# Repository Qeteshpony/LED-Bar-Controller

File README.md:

# Qeteshs 2-Color LED Bar Controller

[Hardware Documentation](https://qeteshpony.github.io/LED-Bar-Controller)

This controller replaces the cable bound remote control for a 2-Color USB LED bar and includes an ESP32-WROOM-32 for connecting it to home automation

The board also features a USB-C port for power, a 3-Pin PH2.0 plug for connecting the LED bar and four buttons to control power, brightness and light-temperature. 

All parts on the top side are selected from the JLCPCB basic library for cheap production. The ESP module and the connectors need manual soldering on the bottom side unless two-sided pcb assembly is used.

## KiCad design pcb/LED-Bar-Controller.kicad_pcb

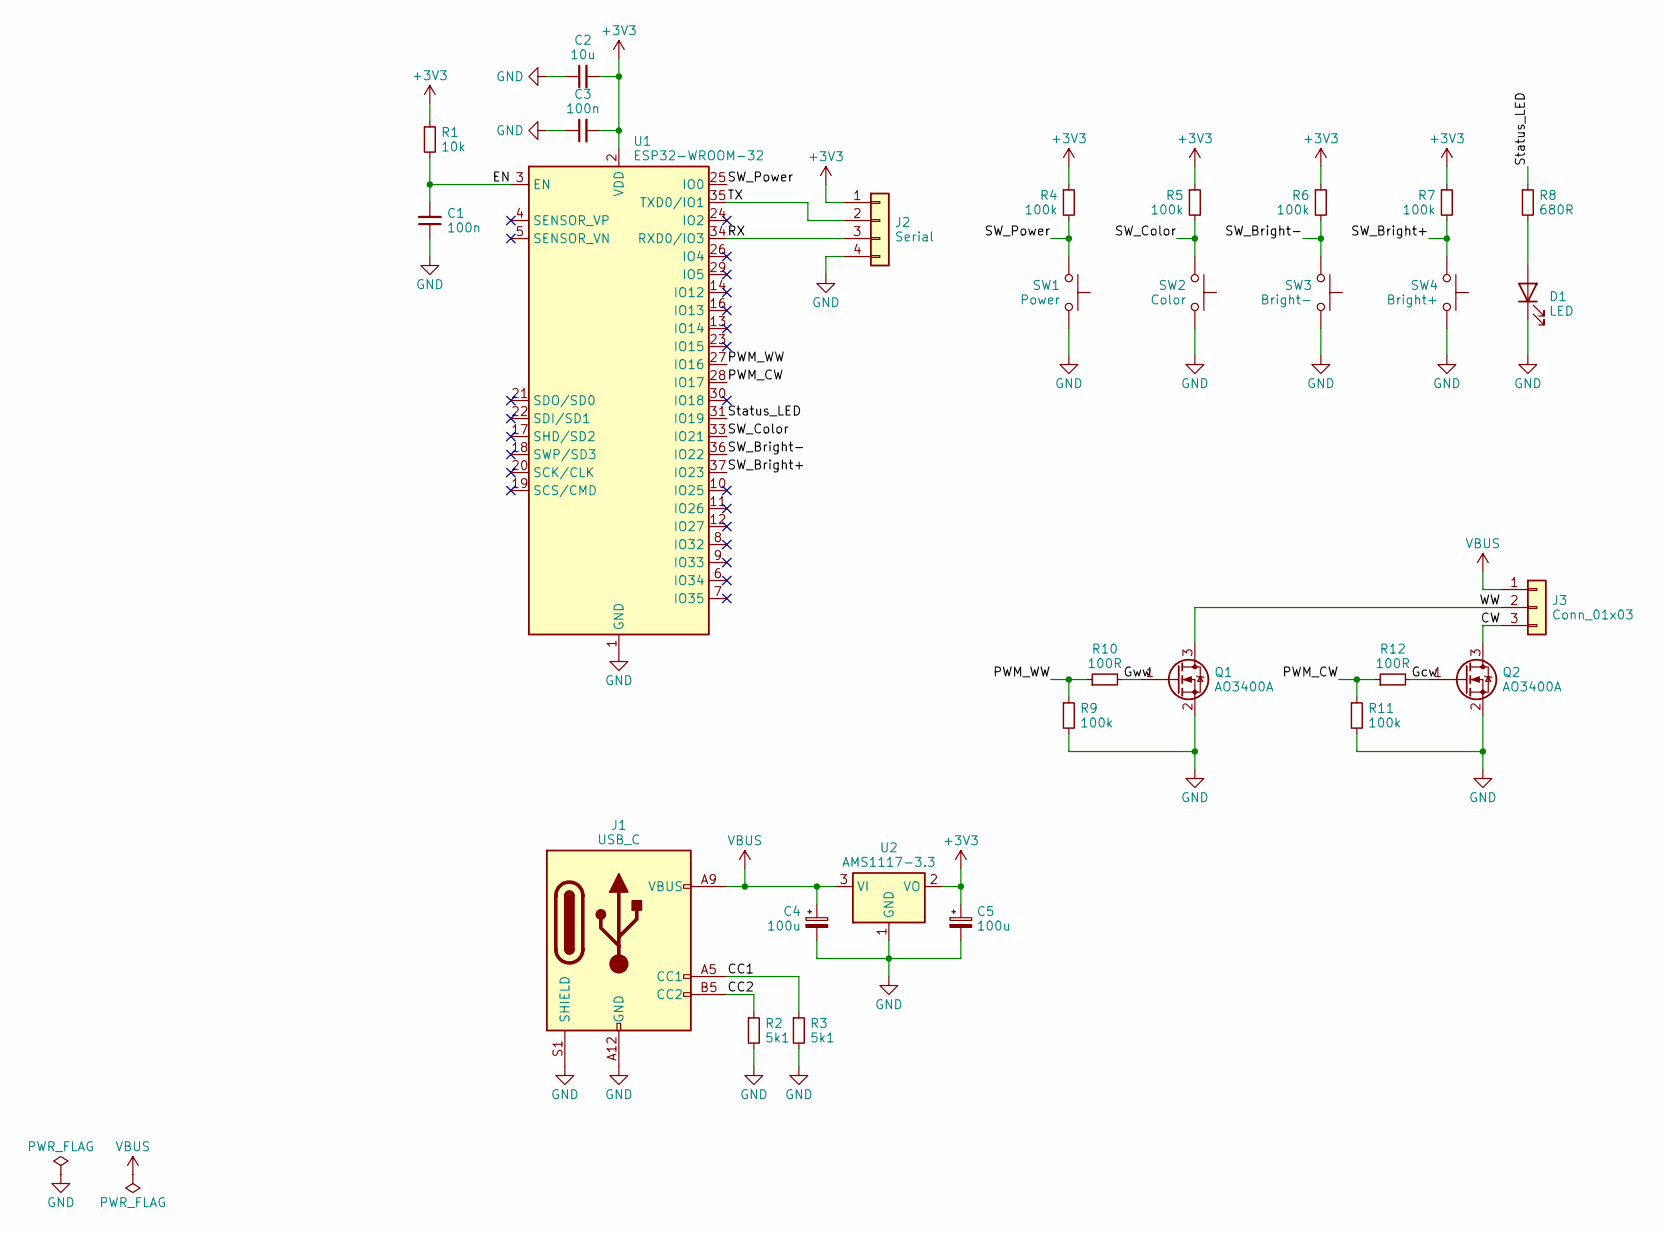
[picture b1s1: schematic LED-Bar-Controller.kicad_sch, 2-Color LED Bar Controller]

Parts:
C1, C3: 100n; C_0402_1005Metric; LCSC C1525
C2: 10u; C_0402_1005Metric; LCSC C15525
C4, C5: 100u; CP_EIA-3528-21_Kemet-B; LCSC C16133
D1: LED; LED_0603_1608Metric; LCSC C2286
J1: USB_C; GCT_USB4125-GF-A_REVA2
J2: Serial; PinSocket_1x04_P2.54mm_Vertical
J3: Conn_01x03; JST_PH_S3B-PH-K_1x03_P2.00mm_Horizontal
Q1, Q2: AO3400A; SOT-23; LCSC C20917
R1: 10k; R_0402_1005Metric; LCSC C25744
R2, R3: 5k1; R_0402_1005Metric; LCSC C25905
R4, R5, R6, R7, R9, R11: 100k; R_0402_1005Metric; LCSC C25741
R8: 680R; R_0603_1608Metric; LCSC C23228
R10, R12: 100R; R_0402_1005Metric; LCSC C25076
SW1: Power; SW_Push_1P1T_XKB_TS-1187A; LCSC C318884
SW2: Color; SW_Push_1P1T_XKB_TS-1187A; LCSC C318884
SW3: Bright-; SW_Push_1P1T_XKB_TS-1187A; LCSC C318884
SW4: Bright+; SW_Push_1P1T_XKB_TS-1187A; LCSC C318884
U1: ESP32-WROOM-32
U2: AMS1117-3.3; SOT-223-3_TabPin2; LCSC C6186

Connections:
+3V3: C2.2, C3.2, C5.1, J2.1, R1.1, R4.1, R5.1, R6.1, R7.1, U1.2 (VDD), U2.2 (VO)
/CC1: J1.A5 (CC1), R3.1
/CC2: J1.B5 (CC2), R2.1
/CW: J3.3, Q2.3 (D)
/EN: C1.2, R1.2, U1.3 (EN)
/Gcw: Q2.1 (G), R12.2
/Gww: Q1.1 (G), R10.2
/PWM_CW: R11.1, R12.1, U1.28 (IO17)
/PWM_WW: R9.1, R10.1, U1.27 (IO16)
/RX: J2.3, U1.34 (RXD0/IO3)
/SW_Bright+: R7.2, SW4.2, U1.37 (IO23)
/SW_Bright-: R6.2, SW3.2, U1.36 (IO22)
/SW_Color: R5.2, SW2.2, U1.33 (IO21)
/SW_Power: R4.2, SW1.2, U1.25 (IO0)
/Status_LED: R8.1, U1.31 (IO19)
/TX: J2.2, U1.35 (TXD0/IO1)
/WW: J3.2, Q1.3 (D)
GND: C1.1, C2.1, C3.1, C4.2, C5.2, D1.1 (K), J1.A12 (GND), J1.B12 (GND), J1.S1 (SHIELD), J2.4, Q1.2 (S), Q2.2 (S), R2.2, R3.2, R9.2, R11.2, SW1.1, SW2.1, SW3.1, SW4.1, U1.1 (GND), U1.15 (GND), U1.38 (GND), U1.39 (GND), U2.1 (GND)
unnamed: D1.2 (A), R8.2
VBUS: C4.1, J1.A9 (VBUS), J1.B9 (VBUS), J3.1, U2.3 (VI)

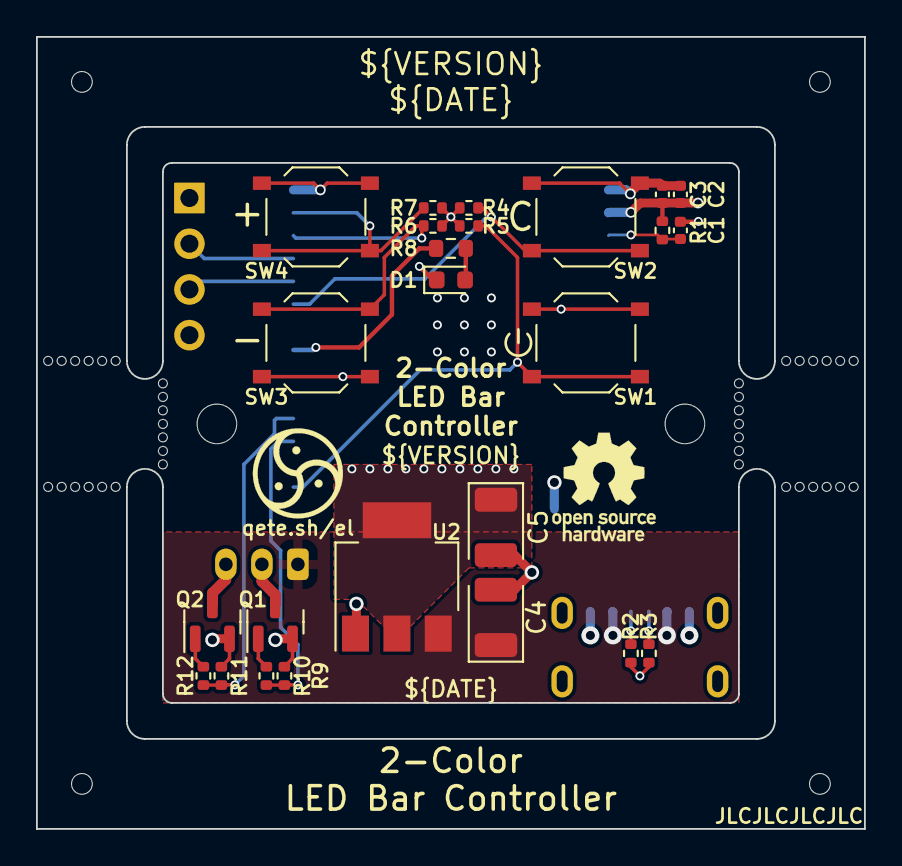
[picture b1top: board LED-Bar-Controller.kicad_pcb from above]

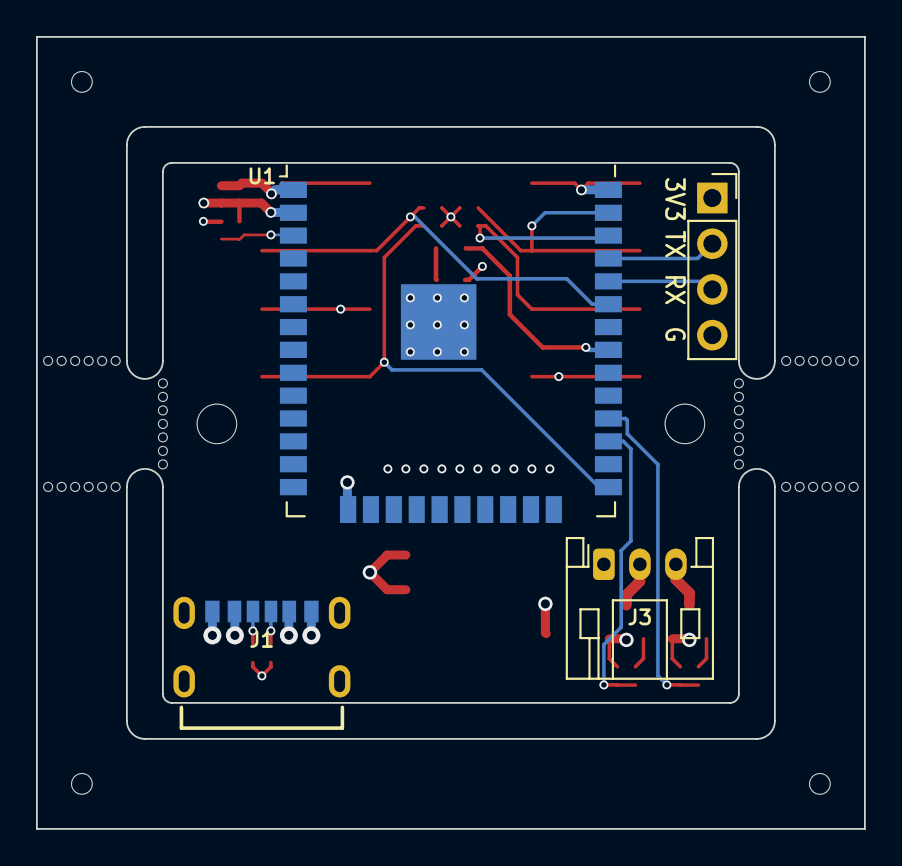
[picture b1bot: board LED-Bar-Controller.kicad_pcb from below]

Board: 4 copper layers, 46.0 x 44.0 mm, 35 parts (4 on the bottom side), 20 nets.

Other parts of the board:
mouse-bite-2mm-slot, mouse-bite-2mm-slot#3, mouse-bite-2mm-slot#5, mouse-bite-2mm-slot#6: VAL**; mouse-bite-5mm-railbreaker
mouse-bite-2mm-slot#2, mouse-bite-2mm-slot#4: VAL**; mouse-bite-2x5mm-slot-onesided-v2

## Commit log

2023-07-22 feat: initial commit
2023-07-22 feat: add JLC part numbers for all basic parts
2023-07-25 fix: switch WW and CW positions
2023-07-25 feat: change button type
    change buttons to type in JLCPCB basic library and change their positions
2023-07-25 fix: improve VBUS connections
2023-07-25 feat: add mouse bites
    Add more mouse bites to make breaking the rails easier
2023-07-25 feat: add origin point
2023-07-25 style: silkscreen cleanup
    Renumber parts and clean up silkscreen positioning
2023-07-25 chore(main): release 1.0.0
2023-07-25 docs: more details
2023-07-25 fix: replace too small vias
    Used too small vias for normal production with JLCPCB
2023-07-25 chore(main): release 1.0.1
2024-08-29 ci: remove dependency between jobs
